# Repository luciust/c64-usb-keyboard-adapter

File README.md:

# Gemini coded - NOT TESTED YET - Commodore 64 USB Keyboard & Wireless Host Adapter (Pico 2 Edition)

A high-performance **Raspberry Pi Pico 2 (RP2350)** bridge that connects modern USB keyboards and 2.4GHz wireless keyboard/mouse combos directly to the Commodore 64 (C64) mainboard keyboard connector (**CN8**).

Leveraging the **5V-tolerant GPIO architecture** of the RP2350, this project eliminates all external level-shifter transceivers, voltage divider resistors, and discrete open-drain diodes, reducing the entire board to just the **Pico 2, the C64 header, and two filter capacitors**.

---

## Key Features

* **Raspberry Pi Pico 2 (RP2350) Architecture:**
  * **5V-Tolerant Digital GPIOs:** GP0–GP16 directly interface with the C64's 5V NMOS CIA 6526 logic lines with **zero external level-shifting ICs**.
  * **Native Open-Drain Matrix Driving:** GP8–GP15 drive the C64 rows in native open-drain mode (0V drive / 5V High-Z), providing 100% hardware immunity against Joystick 1 bus contention.
  * **Direct RESTORE Key Driving:** GP16 drives the C64 Pin 3 (/RESTORE active-low NMI) directly in open-drain mode without extra transistors.
* **USB Host & Wireless Combo Support:**
  * Supports standard USB keyboards (104/105-key HID).
  * Supports **2.4GHz wireless combo dongles** (e.g. Logitech Unifying, Dell, HP) with composite keyboard + mouse interfaces.
  * Safely filters mouse reports while processing keyboard keystrokes.
* **Zero-Latency Real-Time Emulation (< 30 ns):**
  * **Core 0:** Runs TinyUSB Host stack, HID parsing, contact pacing, and USB enumeration.
  * **Core 1:** Dedicated real-time matrix engine monitoring C64 CIA 1 Port A column strobes and toggling row output enables in $< 30\text{ ns}$ (over 100× faster than the 1 MHz 6510 CPU read cycle).
* **KERNAL Debounce & Pacing Filter:**
  * Enforces a $35\text{ ms}$ minimum contact hold time (`C64_MIN_HOLD_TIME_US`) across multiple 50Hz/60Hz C64 vertical interrupt frames ($EA87) to ensure 100% key registration during fast typing.
* **Ultra-Simple Hardware Construction:**
  * Strictly **100% Through-Hole Technology (THT) and DIP** components.
  * Board dimensions: **60.0 mm × 58.0 mm** compact backpack format.
  * Complete **KiCad 8** schematic and 2-layer PCB layout project included.

---

## Project Structure

```
├── bin/
│   ├── c64_usb_keyboard_pico2.uf2  # Pre-built firmware for Raspberry Pi Pico 2 (RP2350)
│   ├── c64_usb_keyboard_pico1.uf2  # Backward-compatible build for Raspberry Pi Pico 1 (RP2040)
│   └── c64_usb_keyboard.uf2        # Default active binary (Pico 2)
├── firmware/
│   ├── CMakeLists.txt              # CMake Pico SDK build configuration
│   ├── pico_sdk_import.cmake       # Pico SDK import script
│   ├── tusb_config.h               # TinyUSB Host stack configuration
│   └── src/
│       ├── main.c                  # Core 0 loop & Core 1 multicore launch
│       ├── c64_matrix.h            # Matrix GPIO definitions and open-drain API
│       ├── c64_matrix.c            # Real-time Core 1 native open-drain engine
│       ├── keymap.h                # USB HID to C64 matrix mapping types & flags
│       ├── keymap.c                # Full 104-key USB to C64 8x8 matrix lookup table
│       ├── usb_hid_host.h          # TinyUSB host interface
│       └── usb_hid_host.c          # HID report parser & combo device handler
├── hardware/
│   ├── BOM.md                      # Ultra-minimal Bill of Materials
│   ├── breadboard_guide.md         # Step-by-step breadboard assembly and test guide
│   ├── PCB_LAYOUT_PROPOSAL.md      # Detailed KiCad 8 PCB layout guide
│   ├── generate_kicad.py           # KiCad 8 project generation script
│   └── kicad/
│       ├── c64_usb_keyboard.kicad_pro  # KiCad 8 project file
│       ├── c64_usb_keyboard.kicad_sch  # KiCad 8 schematic file
│       └── c64_usb_keyboard.kicad_pcb  # KiCad 8 2-layer PCB layout file
└── docs/
    └── voltage_level_research.md   # In-depth research on RP2350 5V tolerance vs RP2040
```

---

## Quick Start: Flashing the Pico 2

1. Connect your **Raspberry Pi Pico 2** to your PC via USB while holding down the **BOOTSEL** button.
2. The board will mount as a mass storage volume named `RP2350`.
3. Drag and drop [`bin/c64_usb_keyboard_pico2.uf2`](bin/c64_usb_keyboard_pico2.uf2) onto the `RP2350` drive.
4. The board will reboot automatically into USB Host bridge mode.

---

## Wiring Summary (C64 Mainboard CN8 $\leftrightarrow$ Pico 2)

| CN8 Pin | Signal | Destination | Function / Notes |
|:---:|:---|:---|:---|
| **1** | GND | Pico 2 GND (Pins 3, 38) | Common Ground reference |
| **2** | KEY | *None* | Polarizing pin (cut on motherboard header) |
| **3** | /RESTORE | Pico 2 GP16 (Pin 21) | Direct native open-drain NMI trigger |
| **4** | +5V DC | Pico 2 VBUS (Pin 40) | Powers Pico 2 & USB Keyboard |
| **5** | Row 3 (PB3) | Pico 2 GP11 (Pin 15) | Native Open-Drain *(via optional 100Ω)* |
| **6** | Row 6 (PB6) | Pico 2 GP14 (Pin 19) | Native Open-Drain *(via optional 100Ω)* |
| **7** | Row 5 (PB5) | Pico 2 GP13 (Pin 17) | Native Open-Drain *(via optional 100Ω)* |
| **8** | Row 4 (PB4) | Pico 2 GP12 (Pin 16) | Native Open-Drain *(via optional 100Ω)* |
| **9** | Row 7 (PB7) | Pico 2 GP15 (Pin 20) | Native Open-Drain *(via optional 100Ω)* |
| **10** | Row 2 (PB2) | Pico 2 GP10 (Pin 14) | Native Open-Drain *(via optional 100Ω)* |
| **11** | Row 1 (PB1) | Pico 2 GP9  (Pin 12) | Native Open-Drain *(via optional 100Ω)* |
| **12** | Row 0 (PB0) | Pico 2 GP8  (Pin 11) | Native Open-Drain *(via optional 100Ω)* |
| **13** | Col 7 (PA7) | Pico 2 GP7  (Pin 10) | Direct 5V-tolerant input |
| **14** | Col 6 (PA6) | Pico 2 GP6  (Pin 9)  | Direct 5V-tolerant input |
| **15** | Col 5 (PA5) | Pico 2 GP5  (Pin 7)  | Direct 5V-tolerant input |
| **16** | Col 4 (PA4) | Pico 2 GP4  (Pin 6)  | Direct 5V-tolerant input |
| **17** | Col 3 (PA3) | Pico 2 GP3  (Pin 5)  | Direct 5V-tolerant input |
| **18** | Col 2 (PA2) | Pico 2 GP2  (Pin 4)  | Direct 5V-tolerant input |
| **19** | Col 1 (PA1) | Pico 2 GP1  (Pin 2)  | Direct 5V-tolerant input |
| **20** | Col 0 (PA0) | Pico 2 GP0  (Pin 1)  | Direct 5V-tolerant input |

---

## Building Firmware from Source

```bash
cd firmware
mkdir -p build && cd build
export PICO_SDK_PATH=/home/lucius/Priv/AGRAVITY/pico-sdk
cmake -DPICO_BOARD=pico2 ..
make -j$(nproc)
```

---

## Documentation Links

* [Voltage Level Shifting & RP2350 5V Tolerance Research](docs/voltage_level_research.md)
* [Breadboard Testing & Prototyping Guide](hardware/breadboard_guide.md)
* [Bill of Materials (Pico 2 Edition)](hardware/BOM.md)
* [PCB Layout Proposal & Design Guide (KiCad 8)](hardware/PCB_LAYOUT_PROPOSAL.md)
* [KiCad 8 Project Directory](hardware/kicad/)

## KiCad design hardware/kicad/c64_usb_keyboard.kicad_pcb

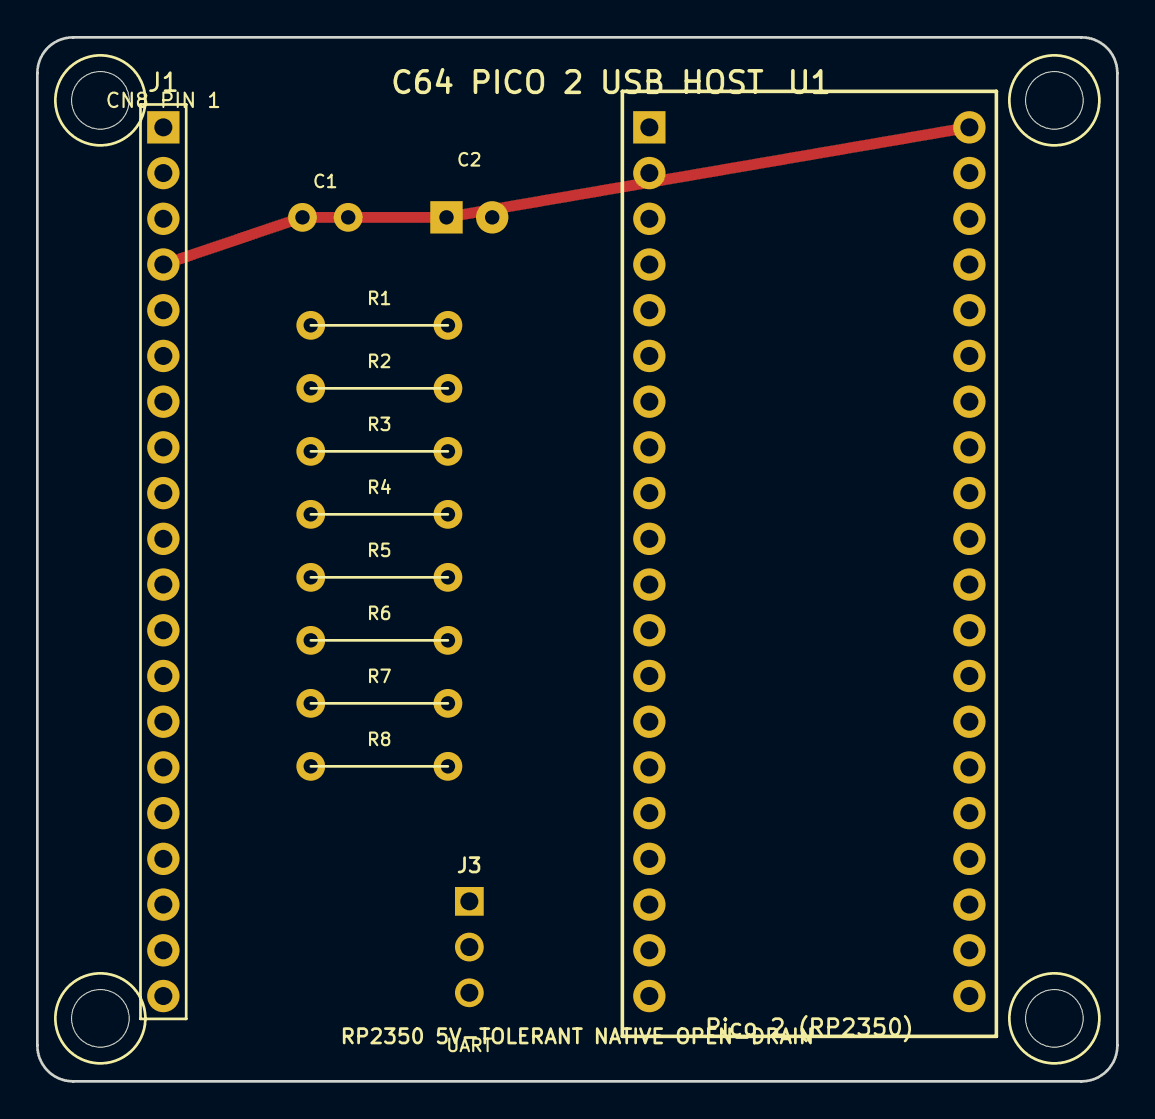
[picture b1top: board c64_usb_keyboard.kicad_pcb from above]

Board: 2 copper layers, 60.0 x 58.0 mm, 17 parts (0 on the bottom side), 27 nets.

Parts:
C1: 100nF; C_Disc_D5.0mm_W2.5mm_P2.54mm
C2: 47uF; CP_Radial_D6.3mm_P2.50mm
H1, H2, H3, H4: MountingHole_3.2mm_M3
J1: C64_CN8; PinHeader_1x20_P2.54mm_Vertical
J3: UART; PinHeader_1x03_P2.54mm_Vertical
R1, R2, R3, R4, R5, R6, R7, R8: 100R; R_Axial_DIN0207_L6.3mm_D2.5mm_P7.62mm_Horizontal
U1: Pico 2 (RP2350); RaspberryPi_Pico_Socket

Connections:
+5V: C1.1, C2.1, J1.4, U1.39, U1.40
C64_COL0: J1.20, U1.1
C64_COL1: J1.19, U1.2
C64_COL2: J1.18, U1.4
C64_COL3: J1.17, U1.5
C64_COL4: J1.16, U1.6
C64_COL5: J1.15, U1.7
C64_COL6: J1.14, U1.9
C64_COL7: J1.13, U1.10
C64_RESTORE: J1.3, U1.21
C64_ROW0: J1.12, R1.1
C64_ROW1: J1.11, R2.1
C64_ROW2: J1.10, R3.1
C64_ROW3: J1.5, R4.1
C64_ROW4: J1.8, R5.1
C64_ROW5: J1.7, R6.1
C64_ROW6: J1.6, R7.1
C64_ROW7: J1.9, R8.1
GND: C1.2, C2.2, J1.1, J3.3, U1.3, U1.8, U1.13, U1.18, U1.23, U1.28, U1.33, U1.38
PICO_ROW0: R1.2, U1.11
PICO_ROW1: R2.2, U1.12
PICO_ROW2: R3.2, U1.14
PICO_ROW3: R4.2, U1.15
PICO_ROW4: R5.2, U1.16
PICO_ROW5: R6.2, U1.17
PICO_ROW6: R7.2, U1.19
PICO_ROW7: R8.2, U1.20

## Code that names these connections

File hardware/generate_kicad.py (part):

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j1_nets = [
    (1, "GND"),         # Pin 1: GND
    (0, "KEY"),         # Pin 2: Key (cut)
    (3, "C64_RESTORE"), # Pin 3: /RESTORE
    (2, "+5V"),         # Pin 4: +5V
    (7, "C64_ROW3"),    # Pin 5: PB3
    (10, "C64_ROW6"),   # Pin 6: PB6
    (9, "C64_ROW5"),    # Pin 7: PB5
    (8, "C64_ROW4"),    # Pin 8: PB4
    (11, "C64_ROW7"),   # Pin 9: PB7
    (6, "C64_ROW2"),    # Pin 10: PB2
    (5, "C64_ROW1"),    # Pin 11: PB1
    (4, "C64_ROW0"),    # Pin 12: PB0
    (19, "C64_COL7"),   # Pin 13: PA7
    (18, "C64_COL6"),   # Pin 14: PA6
    (17, "C64_COL5"),   # Pin 15: PA5
    (16, "C64_COL4"),   # Pin 16: PA4
    (15, "C64_COL3"),   # Pin 17: PA3
    (14, "C64_COL2"),   # Pin 18: PA2
    (13, "C64_COL1"),   # Pin 19: PA1
    (12, "C64_COL0"),   # Pin 20: PA0
]

footprints_str += f"""\t(footprint "Connector_PinHeader_2.54mm:PinHeader_1x20_P2.54mm_Vertical"
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"""
# Pico Left Header (Pins 1-20: GP0-GP15)
pico_left_nets = [
    (12, "C64_COL0"),  # Pin 1: GP0 (Direct 5V-tolerant input)
    (13, "C64_COL1"),  # Pin 2: GP1 (Direct 5V-tolerant input)
    (1, "GND"),        # Pin 3: GND
    (14, "C64_COL2"),  # Pin 4: GP2 (Direct 5V-tolerant input)
    (15, "C64_COL3"),  # Pin 5: GP3 (Direct 5V-tolerant input)
    (16, "C64_COL4"),  # Pin 6: GP4 (Direct 5V-tolerant input)
    (17, "C64_COL5"),  # Pin 7: GP5 (Direct 5V-tolerant input)
    (1, "GND"),        # Pin 8: GND
    (18, "C64_COL6"),  # Pin 9: GP6 (Direct 5V-tolerant input)
    (19, "C64_COL7"),  # Pin 10: GP7 (Direct 5V-tolerant input)
    (20, "PICO_ROW0"), # Pin 11: GP8 (Native Open-Drain)
    (21, "PICO_ROW1"), # Pin 12: GP9 (Native Open-Drain)
    (1, "GND"),        # Pin 13: GND
    (22, "PICO_ROW2"), # Pin 14: GP10 (Native Open-Drain)
    (23, "PICO_ROW3"), # Pin 15: GP11 (Native Open-Drain)
    (24, "PICO_ROW4"), # Pin 16: GP12 (Native Open-Drain)
    (25, "PICO_ROW5"), # Pin 17: GP13 (Native Open-Drain)
    (1, "GND"),        # Pin 18: GND
    (26, "PICO_ROW6"), # Pin 19: GP14 (Native Open-Drain)
    (27, "PICO_ROW7"), # Pin 20: GP15 (Native Open-Drain)
]
for idx, (net_id, net_name) in enumerate(pico_left_nets):
    p_num = idx + 1
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    (0, "GP18"),        # Pin 24: GP18
    (1, "GND"),         # Pin 23: GND
    (0, "GP17"),        # Pin 22: GP17
    (3, "C64_RESTORE"), # Pin 21: GP16 (Direct Native Open-Drain)
]
for idx, (net_id, net_name) in enumerate(pico_right_nets):
    p_num = 40 - idx
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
